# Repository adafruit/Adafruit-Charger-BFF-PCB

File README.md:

## Adafruit Charger BFF for QT Py PCB

<a href="http://www.adafruit.com/products/5397"><br/>
Click here to purchase one from the Adafruit shop</a>

PCB files for the Adafruit Charger BFF for QT Py. 

Format is EagleCAD schematic and board layout
* https://www.adafruit.com/product/5397

### Description

Is your QT Py all alone, lacking a friend to travel the wide world with? When you were a kid you may have learned about the "buddy" system, well this product is kinda like that! A board that will watch your QT Py's back and give it the power and support to wander out past your USB port.

This little lipo charger is designed to fit onto the back of any QT Py board, and make it easy for portable powering. Simply plug any standard 3.7V/4.2V lithium polymer or lithium-ion rechargeable battery into the JST plug on the end. When powered by the USB port on the QT Py, the charger kicks in and will charge up the battery at 200mA max rate. You'll see the yellow LED light up when that happens.

When the USB is removed, the battery will reverse charge into the 5V port via a Schottky diode. You can turn it on or off with the built in slide switch as well.

A simple voltage divider on the cathode side of the diode and connected to pin A2 will let your firmware detect basic modes: if the voltage is over 4.3V, it is probably plugged into USB. If the voltage is 4.2V or below its probably running on the Lipoly battery and you can roughly determine the battery state.

We include some header that you can solder to your QT Py. You can also pick up an Itsy Bitsy short female header kit to make it removable but compact, you'll just need to trim down the headers to 7 pins long.

For use with Adafruit LiPoly/LiIon batteries only! Other batteries may have different voltage, chemistry, polarity, or pinout.

* Comes as an assembled and tested PCB
* Uses the 5V input via USB Type-C connector on QT Py
* For charging single Lithium Ion/Lithium Polymer 3.7/4.2v batteries (not for older 3.6/4.1v cells)
* 200mA charge current

Batteries and QT Py are not included.

<b>Revision History:

* As of December 12, 2025 - </b> We added two breakout pads for the on/off switch for an external switch if desired. We also updated the PCB with Adafruit Pinguin to make a lovely and legible silkscreen.

### License

Adafruit invests time and resources providing this open source design, please support Adafruit and open-source hardware by purchasing products from [Adafruit](https://www.adafruit.com)!

Designed by Limor Fried/Ladyada for Adafruit Industries.

Creative Commons Attribution/Share-Alike, all text above must be included in any redistribution. 
See license.txt for additional details.

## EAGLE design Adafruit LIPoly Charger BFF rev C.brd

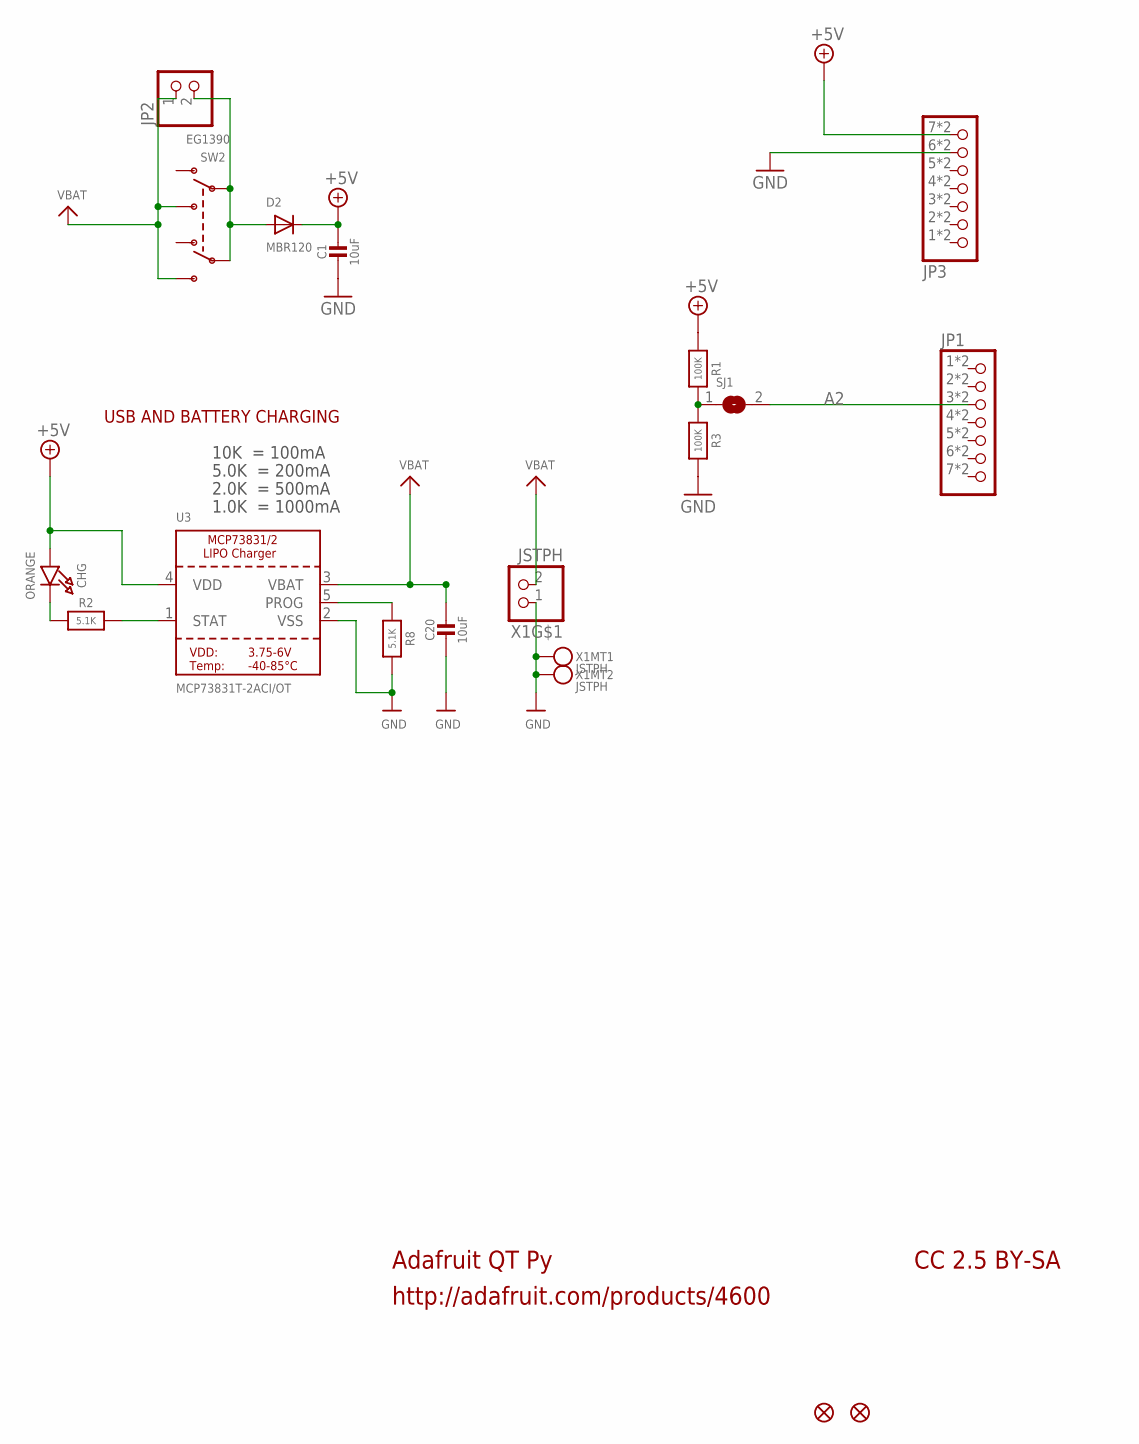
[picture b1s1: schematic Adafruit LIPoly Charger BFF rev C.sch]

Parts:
C1, C20: 10uF; 0805-NO
CHG: ORANGE; CHIPLED_0603_NOOUTLINE
D2: MBR120; SOD-123FL
JP1, JP3: HEADER-1X7_CASTEL; 1X07_CASTEL
JP2: HEADER-1X2ROUND; 1X02_ROUND
R1, R3: 100K; 0603-NO
R2, R8: 5.1K; 0603-NO
SJ1: SOLDERJUMPERCLOSED; SOLDERJUMPER_CLOSEDWIRE
SW2: EG1390
U3: MCP73831T-2ACI/OT; SOT23-5
U$6, U$8: FIDUCIAL_0.5MM
X1: JSTPH; JSTPH2_BATT

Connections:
+5V: C1.1, CHG.A, D2.C, JP3.7, JP3.7C (7), R1.1, U3.4 (VDD)
A2: JP1.3, JP1.3C (3), SJ1.2
GND: C1.2, C20.2, JP3.6, JP3.6C (6), R3.2, R8.2, U3.2 (VSS), X1.1, X1.NC1, X1.NC2
unnamed: R1.2, R3.1, SJ1.1
unnamed: CHG.C, R2.1
unnamed: R2.2, U3.1 (STAT)
unnamed: R8.1, U3.5 (PROG)
unnamed: D2.A, JP2.2, SW2.P1, SW2.P2
VBAT: C20.1, JP2.1, SW2.S1, SW2.S2, U3.3 (VBAT), X1.2

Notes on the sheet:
Adafruit QT Py
http://adafruit.com/products/4600
CC 2.5 BY-SA
10K = 100mA
5.0K = 200mA
2.0K = 500mA
1.0K = 1000mA
USB AND BATTERY CHARGING

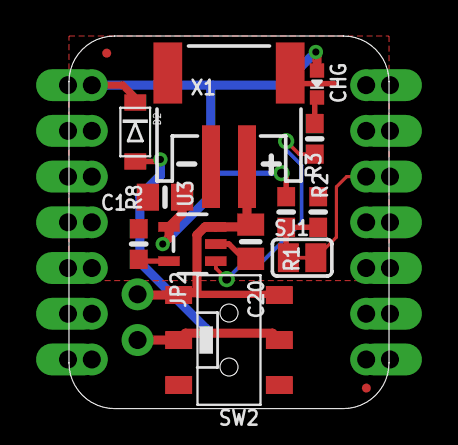
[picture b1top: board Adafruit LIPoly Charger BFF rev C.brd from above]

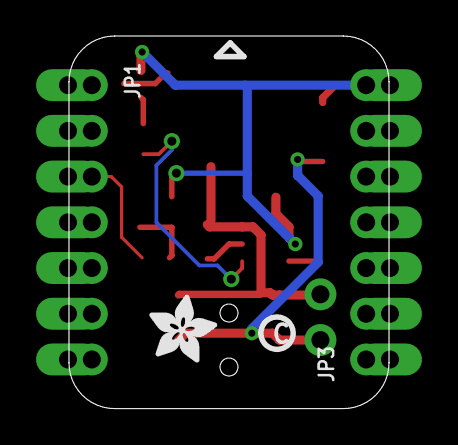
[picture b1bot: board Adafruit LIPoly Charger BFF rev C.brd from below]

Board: 2 copper layers, 17.8 x 20.7 mm, 34 parts (7 on the bottom side), 9 nets.

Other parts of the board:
PLABEL0: PLABEL0
PLABEL1: PLABEL1
PLABEL2: PLABEL2
PLABEL3: PLABEL3
PLABEL4: PLABEL4
PLABEL5: PLABEL5
PLABEL6: PLABEL6
PLABEL7: PLABEL7
PLABEL8: PLABEL8
PLABEL9: PLABEL9
PLABEL10: PLABEL10
PLABEL11: PLABEL11
PLABEL12: PLABEL12
PLABEL13: PLABEL13
PLABEL14: PLABEL14
U$2: ADAFRUIT_3.5MM
U$3: PCBFEAT-REV-040

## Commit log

2022-04-08 Adding board files.
2025-12-19 rev c

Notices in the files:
parts and their libraries:
microbuilder: This work is placed in the public domain, and may be freely used for commercial and non-commercial work with the following conditions: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
